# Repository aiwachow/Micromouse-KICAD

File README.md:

# Micromouse 2.0 class robot 
Micromouse is a autonomous robot whose purpose is to drive through the maze in the shortest time. 
This design include microcontrollers like STM32 and ESP32. Esp was added to testing over-the-air update  
and wireless communication for STM32. Walls are detecting by IR diodes and phototransistors. 

## Used software: 
 
## Things that have been tested and work:
- [x] Hardware 
- [x] STM32, flashing via ST-LINK  
- [x] Dc motors (with driver)
- [x] Encoders 
- [x] Proximity sensor 
- [ ] ESP32

## Software 

In the future, there will be a description of two approaches to the robot's software, as two two-person teams are working on the project.

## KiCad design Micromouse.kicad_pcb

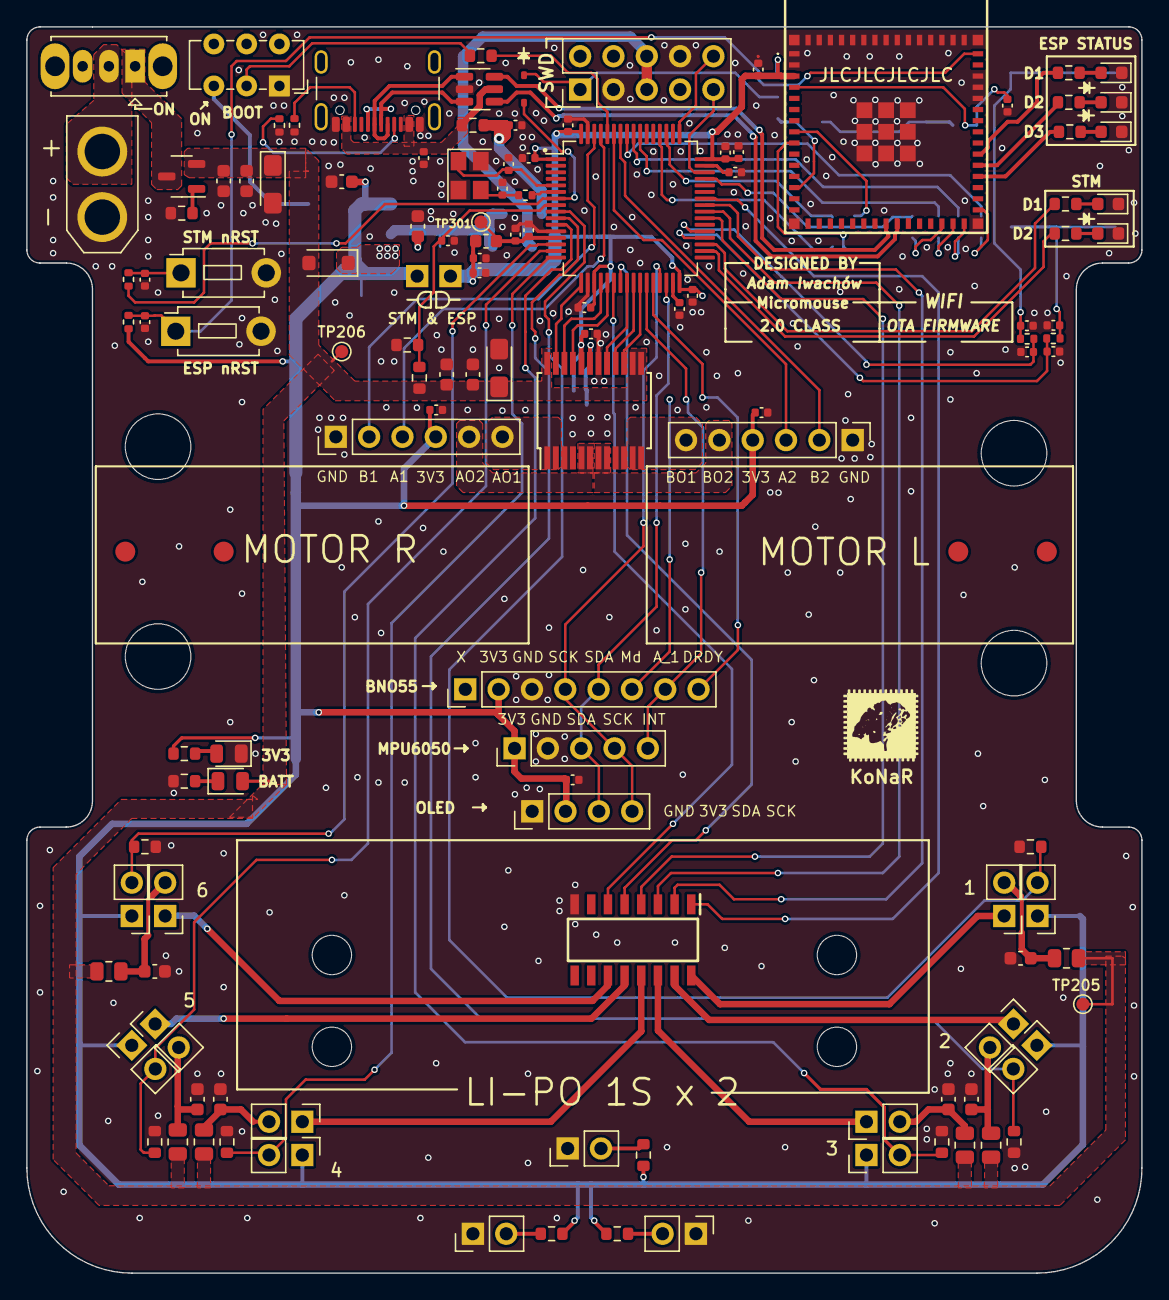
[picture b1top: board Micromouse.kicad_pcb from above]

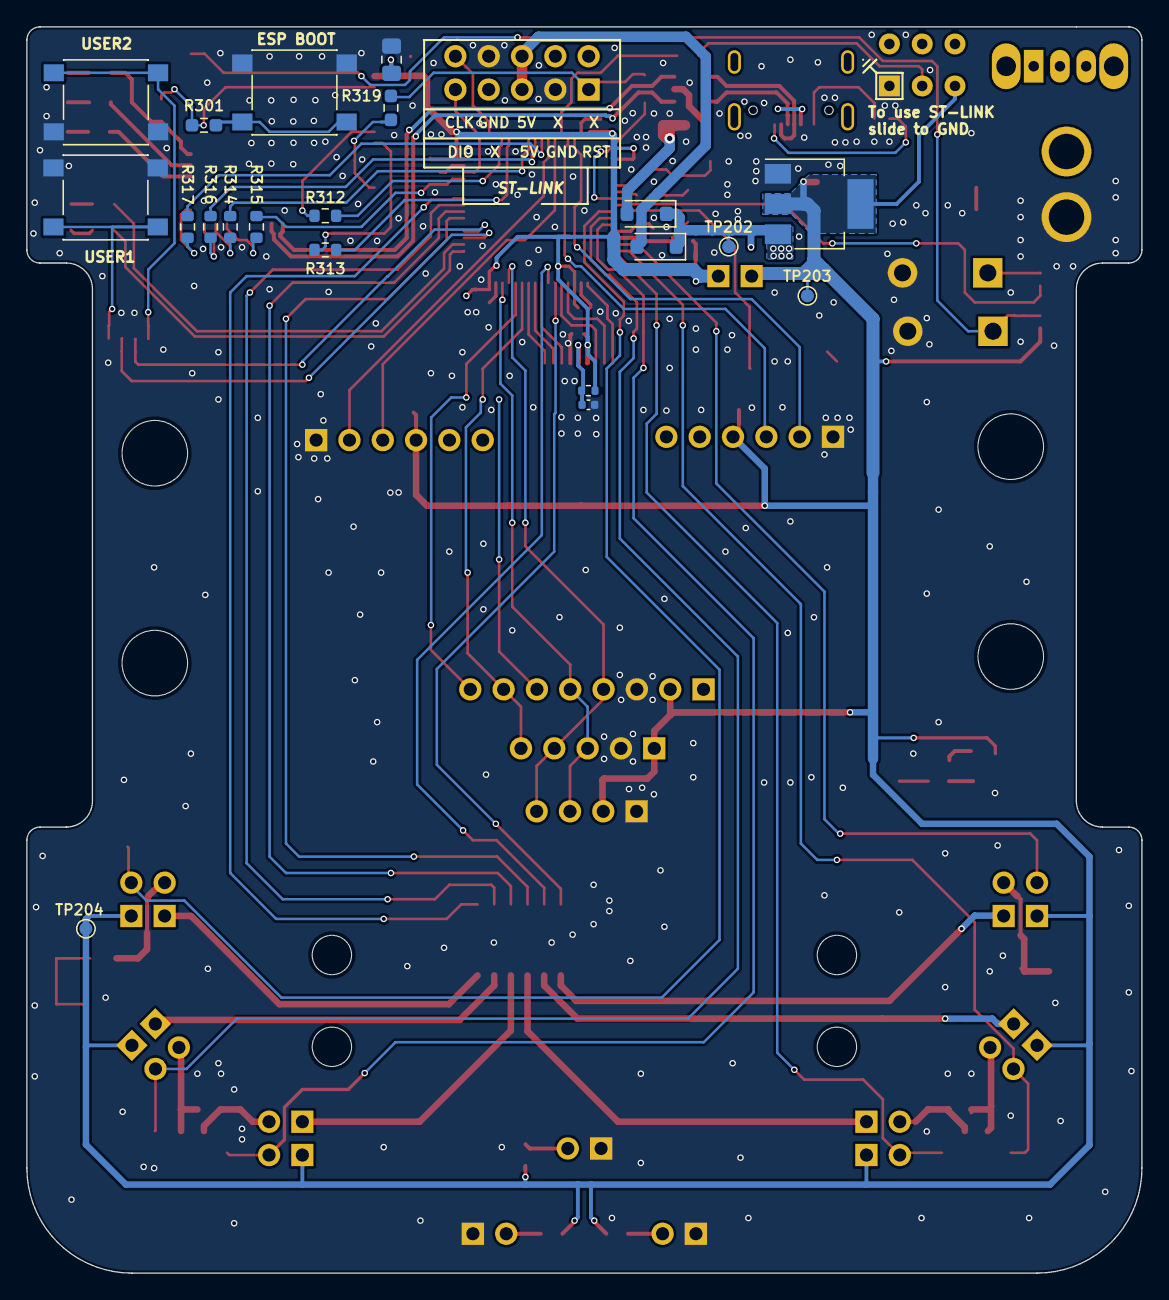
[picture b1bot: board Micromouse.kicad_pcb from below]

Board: 2 copper layers, 85.0 x 95.0 mm, 153 parts (20 on the bottom side), 108 nets.

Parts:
C201, C304, C306, C307, C309, C310, C312, C314, C315, C316, C317, C318, C319, C320, C321, C323, C324, C401, C404, C405, C406: 100n; C_0402_1005Metric
C202, C403, C407, C501, C502, C503, C504, C505, C506: 100n; C_0603_1608Metric
C203, C207: 1u; C_0603_1608Metric
C204, C308: 4u7; C_0402_1005Metric
C205, C402: 10u; CP_EIA-3216-10_Kemet-I_Pad1.58x1.35mm_HandSolder
C206: 10n; C_0402_1005Metric
C208: 4u7; C_0603_1608Metric
C301, C303: 1u; C_0402_1005Metric
C302, C305: 10p; C_0402_1005Metric
C311, C313: 2u2; C_0402_1005Metric
C322: 10u; C_0805_2012Metric_Pad1.18x1.45mm_HandSolder
D201, D202, D203: D_Schottky; D_SOD-123FL
D204: BATT_LED; LED_0805_2012Metric
D205: 3V3_LED; LED_0805_2012Metric
D302, D303, D305, D306, D307: LED_WHITE; D_0603_1608Metric
D304: D_Schottky; D_SOD-323
D501, D507, D509: SFH 4550; PinHeader_1x02_P2.54mm_Vertical
D502, D503, D504, D505, D506, D508: LED; PinHeader_1x02_P2.54mm_Vertical
FB301: Optionally; L_0603_1608Metric
H201, H202, H203, H204: MountingHole; MountingHole_3mm
H401, H402, H403, H404: MountingHole; MountingHole_5mm
IC302: ESP32-S3-MINI-1-N8; ESP32S3MINI1N8
IC501: ULN2003ADR; SOIC127P600X175-16N
J201: XT30; AMASS_XT30U-M_1x02_P5.0mm_Vertical
J202: USB_C_Receptacle_USB2.0; USB_C_Receptacle_GCT_USB4105-xx-A_16P_TopMnt_Horizontal
J301: Conn_02x05_Counter_Clockwise; PinHeader_2x05_P2.54mm_Vertical
J302: Conn_01x04; PinHeader_1x04_P2.54mm_Vertical
J401, J402: Conn_01x06; PinHeader_1x06_P2.54mm_Vertical
J601: Conn_01x08; PinHeader_1x08_P2.54mm_Vertical
J602: Conn_01x05; PinHeader_1x05_P2.54mm_Vertical
JP201: Jumper_2_Bridged; PinHeader_1x02_P2.54mm_Vertical
Q201: PMOS; SOT-23-3
Q501: SFH 300 FA-3/4; PinHeader_1x02_P2.54mm_Vertical
Q502, Q503, Q504, Q505, Q506: Q_Photo_NPN; PinHeader_1x02_P2.54mm_Vertical
R201, R202: 5k1; R_0402_1005Metric
R203, R306: 10k; R_0603_1608Metric
R204: 0; R_0603_1608Metric
R205: 82k; R_0603_1608Metric
R206: 51k; R_0603_1608Metric
R207: 2k2; R_0603_1608Metric
R208: 1K; R_0603_1608Metric
R301: 1k; R_0603_1608Metric_Pad0.98x0.95mm_HandSolder
R302, R305, R309, R310, R318, R501, R503, R505, R507, R509, R511, R513, R514, R515: 1k; R_0603_1608Metric
R303: 22; R_0402_1005Metric
R304, R311, R401: 10k; R_0402_1005Metric
R307, R308: 1k; R_0402_1005Metric
R312, R313: 100; R_0603_1608Metric
R314, R315, R316, R317: 22; R_0603_1608Metric
R319: 0; R_0603_1608Metric_Pad0.98x0.95mm_HandSolder
R502, R504, R506, R508, R510, R512: 47; R_0805_2012Metric
SW201: SW_SPDT; SW_Slide_1P2T_CK_OS102011MS2Q
SW301: NRST; SW_PUSH_1P1T_6x3.5mm_H4.3_APEM_MJTP1243
SW302: SW_SPDT; SW_E-Switch_EG1271_SPDT
SW303, SW304: USER; SW_Push_1P1T_NO_6x6mm_H9.5mm
SW305: ESP_RST; SW_PUSH_1P1T_6x3.5mm_H4.3_APEM_MJTP1243
SW306: BOOT; SW_Push_1P1T_NO_6x6mm_H9.5mm
TP202, TP203, TP204, TP205, TP206, TP301: TestPoint; TestPoint_Pad_D1.0mm
U201: USBLC6-2SC6; SOT-23-6
U202: LDL1117S33R; SOT-223-3_TabPin2
U301: STM32F405RGT6; LQFP-64_10x10mm_P0.5mm
U401: TB6612FNG; SSOP-24_5.3x8.2mm_P0.65mm
Y301: 16MHz|9p|10ppm; Crystal_SMD_3225-4Pin_3.2x2.5mm

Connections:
5V_ST: D203.2 (A), J301.5, J301.6
+3.3V: C208.1, C301.1, C306.1, C308.1, C309.1, C310.1, C312.1, C314.1, C315.1, C321.1, C322.1, C323.1, C404.1, C405.1, C406.1, FB301.1, IC302.3 (3V3), J302.2 (Pin_1), J401.4 (Pin_1), J402.4 (Pin_1), J601.2, J602.1, JP201.1 (A), JP201.2 (B), Q501.1 (C), Q502.1 (C), Q503.1 (C), Q504.1 (C), Q505.1 (C), Q506.1 (C), R208.1, R311.2, R401.1, R513.2, R514.2, R515.2, SW302.3 (C), TP203.1, TP204.1, U202.2 (VO), U301.1 (VBAT), U301.19 (VDD), U301.32 (VDD), U301.48 (VDD), U301.64 (VDD), U401.20 (VCC)
+3.3VA: C303.1, C307.1, FB301.2, TP301.1, U301.13 (VDDA)
+BATT: C202.1, C203.1, C205.1, C402.1, C403.1, C407.1, D202.2 (A), D204.2 (A), Q201.2 (S), R205.2, R502.1, R504.1, R506.1, R508.1, R510.1, R512.1, TP205.1, TP206.1, U401.13 (VM2), U401.14 (VM3), U401.24 (VM1)
/Distance_sensors/Emitter1A: C504.1, D504.2 (A), R508.2
/Distance_sensors/Emitter2A: C503.1, D503.2 (A), R506.2
/Distance_sensors/Emitter3A: C502.1, D502.2 (A), R504.2
/Distance_sensors/Emitter4A: C501.1, D501.2 (A), R502.2
/Distance_sensors/Emitter5A: C505.1, D505.2 (A), R510.2
/Distance_sensors/Emitter6A: C506.1, D506.2 (A), R512.2
/Distance_sensors/Emitter_1: D504.1 (K), IC501.13 (4C)
/Distance_sensors/Emitter_2: D503.1 (K), IC501.14 (3C)
/Distance_sensors/Emitter_3: D502.1 (K), IC501.15 (2C)
/Distance_sensors/Emitter_4: D501.1 (K), IC501.16 (1C)
/Distance_sensors/Emitter_5: D505.1 (K), IC501.12 (5C)
/Distance_sensors/Emitter_6: D506.1 (K), IC501.11 (6C)
/Microcontroller/HSE OUT: C305.1, R303.2, Y301.3
/Microcontroller/OTA_RX: IC302.9 (IO5), R313.2
/Microcontroller/OTA_TX: IC302.8 (IO4), R312.2
/Microcontroller/USER_LD2_A: D302.2 (A), R302.2
/Microcontroller/USER_LD2_A_esp: D306.2 (A), R310.2
/Microcontroller/USER_LD3_A: D303.2 (A), R305.2
/Microcontroller/USER_LD3_A_esp: D307.2 (A), R318.2
/Microcontroller/USER_LD_A_esp: D305.2 (A), R309.2
/Motors/AO1: J401.6 (Pin_3), U401.1 (AO1), U401.2 (AO1)
/Motors/AO2: J401.5, U401.5 (AO2), U401.6 (AO2)
/Motors/BO1: J402.6 (Pin_3), U401.11 (BO1), U401.12 (BO1)
/Motors/BO2: J402.5, U401.7 (BO2), U401.8 (BO2)
/Power/8V_BATT: J201.2, SW201.2 (B)
/Power/DN: J202.A7 (D-), J202.B7 (D-), U201.1 (I/O1)
/Power/DP: J202.A6 (D+), J202.B6 (D+), U201.3 (I/O2)
/Power/D_PMOS: Q201.3 (D), SW201.1 (A)
/Power/LDO_VIN: C207.1, D201.1 (K), D202.1 (K), D203.1 (K), TP202.1, U202.3 (VI)
/Power/usb_vin: C204.1, D201.2 (A), R204.2
BOOT: C324.1, IC302.4 (IO0), R301.2
BatteryLEVEL: C206.1, R205.1, R206.2, U301.8 (PC0)
DRDY: J601.8 (Pin_3), U301.28 (PB2)
ESP_USB_DN: IC302.23 (IO19), U201.6 (I/O1)
ESP_USB_DP: IC302.24 (IO20), U201.4 (I/O2)
GND: C201.2, C202.2, C203.2, C204.2, C205.2, C206.2, C207.2, C208.2, C301.2, C302.2, C303.2, C304.2, C305.2, C306.2, C307.2, C308.2, C309.2, C310.2, C311.2, C312.2, C313.2, C314.2, C315.2, C316.2, C317.2, C318.1, C319.1, C320.2, C321.2, C322.2, C323.2, C324.2, C401.2, C402.2, C403.2, C404.2, C405.2, C406.2, C407.2, C501.2, C502.2, C503.2, C504.2, C505.2, C506.2, D205.1 (K), D302.1 (K), D303.1 (K), D305.1 (K), D306.1 (K), D307.1 (K), D507.1 (K), D508.1 (K), D509.1 (K), IC302.1 (GND_1), IC302.2 (GND_2), IC302.41 (IO45), IC302.42 (GND_3), IC302.43 (GND_4), IC302.46 (GND_5), IC302.47 (GND_6), IC302.48 (GND_7), IC302.49 (GND_8), IC302.50 (GND_9), IC302.51 (GND_10), IC302.52 (GND_11), IC302.53 (GND_12), IC302.54 (GND_13), IC302.55 (GND_14), IC302.56 (GND_15), IC302.57 (GND_16), IC302.58 (GND_17), IC302.59 (GND_18), IC302.60 (GND_19), IC302.61 (GND_20), IC302.62 (GND_21), IC302.63 (GND_22), IC302.64 (GND_23), IC302.65 (GND_24), IC302.66 (GND_25), IC302.67 (GND_26), IC302.68 (GND_27), IC302.69 (GND_28), IC302.70 (GND_29), IC302.71 (GND_30), IC302.72 (GND_31), IC302.73 (GND_32), IC501.8 (E), J201.1, J202.A1 (GND), J202.A12 (GND), J202.B1 (GND), J202.B12 (GND), J301.3, J301.8, J302.1 (Pin_4), J401.1 (Pin_6), J402.1 (Pin_6), J601.3 (Pin_8), J602.2 (Pin_5), R201.2, R202.2, R203.1, R206.1, R207.1, R501.1, R503.1, R505.1, R507.1, R509.1, R511.1, SW301.2 (B), SW302.1 (A), SW303.2 (B), SW304.2 (B), SW305.2 (B), SW306.2 (B), U201.2 (GND), U202.1 (GND), U301.12 (VSSA), U301.18 (VSS), U301.63 (VSS), U401.3 (PGND1), U401.4 (PGND1), U401.9 (PGND2), U401.10 (PGND2), U401.18 (GND), Y301.2, Y301.4
HSE_IN: C302.1, U301.5 (PH0), Y301.1
HSE_OUT: R303.1, U301.6 (PH1)
I2C1_SCK: J302.4 (Pin_3), J601.4, J602.4, U301.29 (PB10)
I2C1_SDA: J302.3 (Pin_2), J601.5, J602.3, U301.30 (PB11)
IMU_INT: J601.7, J602.5 (Pin_2), U301.27 (PB1)
IR_1: IC501.4 (4B), U301.39 (PC8)
IR_2: IC501.3 (3B), U301.40 (PC9)
IR_3: IC501.2 (2B), U301.41 (PA8)
IR_4: IC501.1 (1B), U301.42 (PA9)
IR_5: IC501.5 (5B), U301.23 (PA7)
IR_6: IC501.6 (6B), U301.22 (PA6)
MotorL_BIN1: U301.24 (PC4), U401.17 (BIN1)
MotorL_BIN2: U301.25 (PC5), U401.16 (BIN2)
MotorL_PWM: U301.26 (PB0), U401.15 (PWMB)
MotorR_AIN1: U301.21 (PA5), U401.21 (AIN1)
MotorR_AIN2: U301.20 (PA4), U401.22 (AIN2)
MotorR_PWM: U301.17 (PA3), U401.23 (PWMA)
NRST: D304.2 (A), R304.2, U301.7 (NRST)
unnamed: C304.1, R304.1, SW301.1 (A)
unnamed: C316.1, R307.1, SW303.1 (A)
unnamed: C319.2, R308.2, SW304.1 (A)
unnamed: D204.1 (K), R207.2
unnamed: D205.2 (A), R208.2
unnamed: D507.2 (A), R513.1
unnamed: D508.2 (A), R514.1
unnamed: D509.2 (A), R515.1
unnamed: C320.1, IC302.45 (EN), R311.1, SW305.1 (A)
unnamed: IC302.13 (IO9), R319.2
unnamed: IC302.28 (IO33), R315.2
unnamed: IC302.29 (IO34), R314.2
unnamed: IC302.31 (IO35), R317.2
unnamed: IC302.30 (IO48), R316.2
unnamed: J202.A5 (CC1), R201.1
unnamed: J202.B5 (CC2), R202.1
unnamed: Q201.1 (G), R203.2
unnamed: R301.1, SW306.1 (A)
unnamed: R306.1, SW302.2 (B)
unnamed: R306.2, U301.60 (BOOT0)
unnamed: C311.1, U301.31 (VCAP_1)
unnamed: C313.1, U301.47 (VCAP_2)
unnamed: C401.1, R401.2, U401.19 (STBY)
REC_1: Q504.2 (E), R507.2, U301.9 (PC1)
REC_2: Q503.2 (E), R505.2, U301.10 (PC2)
REC_3: Q502.2 (E), R503.2, U301.11 (PC3)
REC_4: Q501.2 (E), R501.2, U301.16 (PA2)
REC_5: Q505.2 (E), R509.2, U301.15 (PA1)
REC_6: Q506.2 (E), R511.2, U301.14 (PA0)
SPI1_CS_ESP: R315.1, U301.45 (PA12)
SPI1_MISO_ESP: R316.1, U301.56 (PB4)
SPI1_MOSI_ESP: R317.1, U301.57 (PB5)
SPI1_SCK_ESP: R314.1, U301.55 (PB3)
SWCLK: J301.10, U301.49 (PA14)
SWDIO: J301.9, U301.46 (PA13)
TIM_ENCODER_A1: J401.3 (Pin_4), U301.61 (PB8)
TIM_ENCODER_A2: J402.3 (Pin_4), U301.59 (PB7)
TIM_ENCODER_B1: J401.2, U301.62 (PB9)
TIM_ENCODER_B2: J402.2, U301.58 (PB6)
UART4_RX_OTA: R313.1, U301.52 (PC11)
UART4_TX_OTA: R312.1, U301.51 (PC10)
USER_B: C317.1, R307.2, U301.36 (PB15)
USER_B2: C318.2, R308.1, U301.37 (PC6)
USER_LD2: R302.1, U301.34 (PB13)
USER_LD2_esp: IC302.35 (IO39), R310.1
USER_LD3: R305.1, U301.35 (PB14)
USER_LD3_esp: IC302.36 (IO40), R318.1
USER_LD_esp: IC302.34 (IO38), R309.1
VBUS: C201.1, J202.A4 (VBUS), J202.A9 (VBUS), J202.B4 (VBUS), J202.B9 (VBUS), R204.1, U201.5 (VBUS)
_NRST: D304.1 (K), J301.1, R319.1

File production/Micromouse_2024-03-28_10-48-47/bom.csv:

Designator,Footprint,Quantity,Value,LCSC Part #
"C201, C304, C306, C307, C309, C310, C312, C314, C315, C316, C317, C318, C319, C320, C321, C323, C324, C401, C404, C405, C406",0402,21,100n,C307331
"C202, C403, C407, C501, C502, C503, C504, C505, C506",0603,9,100n,C14663
"C203, C207",0603,2,1u,C15849
C204,0402,1,4u7,C23733
"C205, C402",CP_EIA-3216-10_Kemet-I_Pad1.58x1.35mm_HandSolder,2,10u,C7171
C206,0402,1,10n,C15195
C208,0603,1,4u7,C19666 
"C301, C303",0402,2,1u,C15849
"C302, C305",0402,2,10p,C32949
C308,0402,1,4u7,C96446
"C311, C313",0402,2,2u2,C12530
C322,0805,1,10u,C307331
"D201, D202, D203",D_SOD-123FL,3,D_Schottky,
D204,0805,1,BATT_LED,C2297
D205,0805,1,3V3_LED,C2297
"D302, D303, D305, D306, D307",0603,5,LED_WHITE,C2290
D304,D_SOD-323,1,D_Schottky,C191023
"D501, D507, D509",PinHeader_1x02_P2.54mm_Vertical,3,SFH 4550,
"D502, D503, D504, D505, D506, D508",PinHeader_1x02_P2.54mm_Vertical,6,LED,
FB301,0603,1,Optionally,C1002
"H201, H202, H203, H204",MountingHole_3mm,4,MountingHole,
"H401, H402, H403, H404",MountingHole_5mm,4,MountingHole,
IC302,ESP32S3MINI1N8,1,ESP32-S3-MINI-1-N8,
IC501,SOIC127P600X175-16N,1,ULN2003ADR,
J201,AMASS_XT30U-M_1x02_P5.0mm_Vertical,1,XT30,
J202,USB_C_Receptacle_GCT_USB4105-xx-A_16P_TopMnt_Horizontal,1,USB_C_Receptacle_USB2.0,
J301,PinHeader_2x05_P2.54mm_Vertical,1,Conn_02x05_Counter_Clockwise,
J302,PinHeader_1x04_P2.54mm_Vertical,1,Conn_01x04,
"J401, J402",PinHeader_1x06_P2.54mm_Vertical,2,Conn_01x06,
J601,PinHeader_1x08_P2.54mm_Vertical,1,Conn_01x08,
J602,PinHeader_1x05_P2.54mm_Vertical,1,Conn_01x05,
JP201,PinHeader_1x02_P2.54mm_Vertical,1,Jumper_2_Bridged,
Q201,SOT-23-3,1,PMOS,C15127
Q501,PinHeader_1x02_P2.54mm_Vertical,1,SFH 300 FA-3/4,
"Q502, Q503, Q504, Q505, Q506",PinHeader_1x02_P2.54mm_Vertical,5,Q_Photo_NPN,
"R201, R202",0402,2,5k1,C25905
R203,0603,1,10k,C25804
R204,0603,1,0,C21189
R205,0603,1,82k,C23254
R206,0603,1,51k,C23196
R207,0603,1,2k2,C4190
"R208, R302, R305, R309, R310, R318, R501, R503, R505, R507, R509, R511, R513, R514, R515",0603,15,1K,C21190
R301,0603,1,1k,
R303,0402,1,22,C25092
"R304, R311, R401",0402,3,10k,C25744
R306,0603,1,10k,C25744
"R307, R308",0402,2,1k,C11702
"R312, R313",0603,2,100,
"R314, R315, R316",0603,3,22,
R317,0603,1,22,
R319,0603,1,0,
"R502, R504, R506, R508, R510, R512",0805,6,47,C17714
SW201,SW_Slide_1P2T_CK_OS102011MS2Q,1,SW_SPDT,
SW301,SW_PUSH_1P1T_6x3.5mm_H4.3_APEM_MJTP1243,1,NRST,
SW302,SW_E-Switch_EG1271_SPDT,1,SW_SPDT,
"SW303, SW304",SW_Push_1P1T_NO_6x6mm_H9.5mm,2,USER,
SW305,SW_PUSH_1P1T_6x3.5mm_H4.3_APEM_MJTP1243,1,ESP_RST,
SW306,SW_Push_1P1T_NO_6x6mm_H9.5mm,1,BOOT,
"TP202, TP203, TP204, TP205, TP206, TP301",TestPoint_Pad_D1.0mm,6,TestPoint,
U201,SOT-23-6,1,USBLC6-2SC6,
U202,SOT-223-3_TabPin2,1,LDL1117S33R,
U301,LQFP-64_10x10mm_P0.5mm,1,STM32F405RGT6,C15742
U401,SSOP-24_5.3x8.2mm_P0.65mm,1,TB6612FNG,
Y301,Crystal_SMD_3225-4Pin_3.2x2.5mm,1,16MHz|9p|10ppm,C13738

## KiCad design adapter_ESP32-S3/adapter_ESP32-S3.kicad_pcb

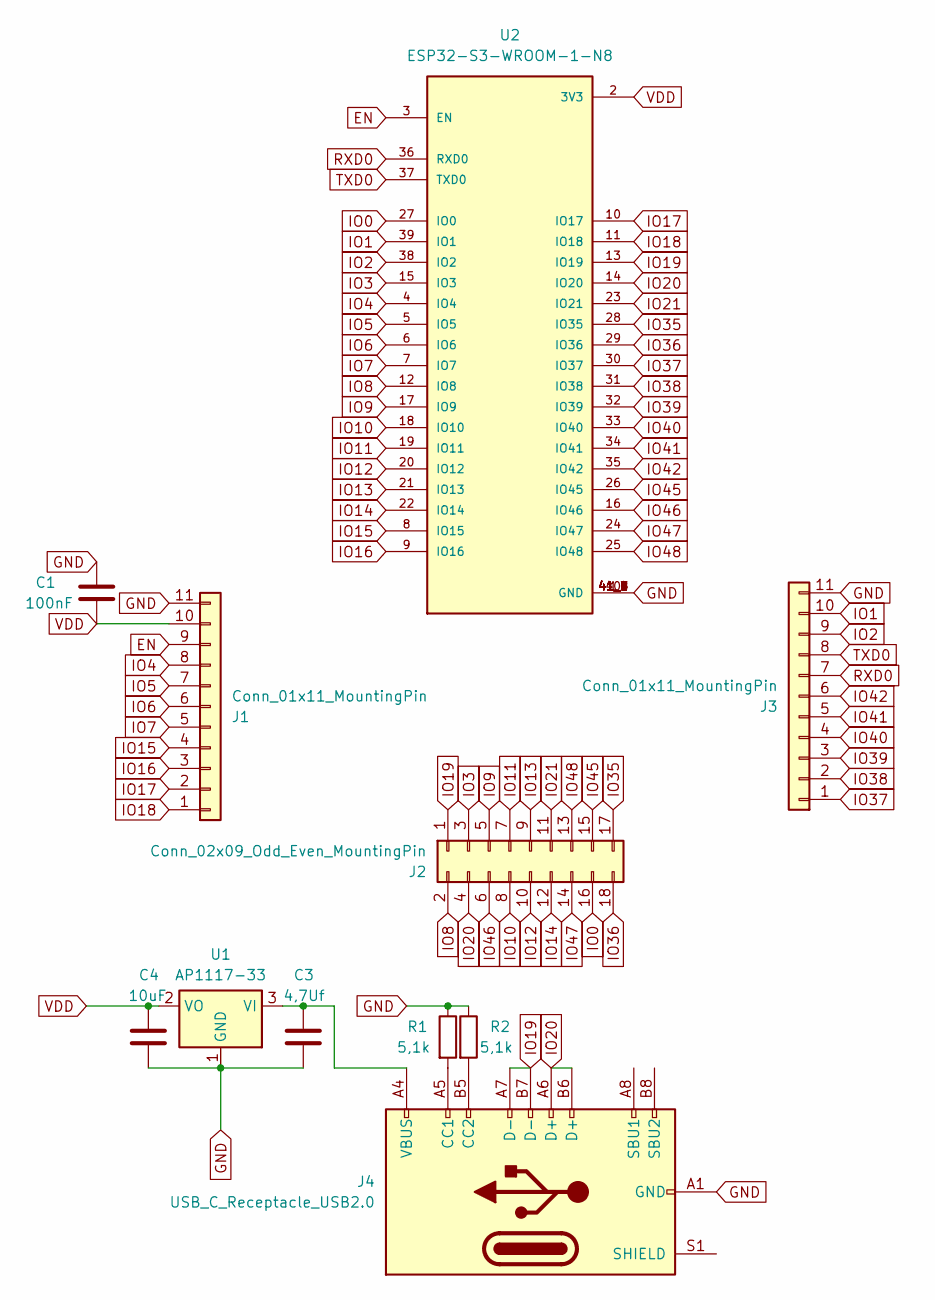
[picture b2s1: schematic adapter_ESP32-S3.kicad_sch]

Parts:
C1: 100nF; C_0603_1608Metric
C3: 4,7Uf; C_0603_1608Metric
C4: 10uF; C_0603_1608Metric
J1, J3: Conn_01x11_MountingPin; PinHeader_1x11_P2.54mm_Vertical
J2: Conn_02x09_Odd_Even_MountingPin; PinHeader_2x09_P2.54mm_Vertical
J4: USB_C_Receptacle_USB2.0; USB_C_Receptacle_GCT_USB4105-xx-A_16P_TopMnt_Horizontal
R1, R2: 5,1k; R_0603_1608Metric
U1: AP1117-33; SOT-223-3_TabPin2
U2: ESP32-S3-WROOM-1-N8; XCVR_ESP32-S3-WROOM-1-N8

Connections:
EN: J1.9, U2.3 (EN)
GND: C1.2, C3.1, C4.1, J1.11, J3.11, J4.A1 (GND), J4.A12 (GND), J4.B1 (GND), J4.B12 (GND), R1.1, R2.1, U1.1 (GND), U2.1 (GND), U2.40 (GND), U2.41_1 (GND), U2.41_2 (GND), U2.41_3 (GND), U2.41_4 (GND), U2.41_5 (GND), U2.41_6 (GND), U2.41_7 (GND), U2.41_8 (GND), U2.41_9 (GND)
IO0: J2.16, U2.27 (IO0)
IO1: J3.10, U2.39 (IO1)
IO2: J3.9, U2.38 (IO2)
IO3: J2.3, U2.15 (IO3)
IO4: J1.8, U2.4 (IO4)
IO5: J1.7, U2.5 (IO5)
IO6: J1.6, U2.6 (IO6)
IO7: J1.5, U2.7 (IO7)
IO8: J2.2, U2.12 (IO8)
IO9: J2.5, U2.17 (IO9)
IO10: J2.8, U2.18 (IO10)
IO11: J2.7, U2.19 (IO11)
IO12: J2.10, U2.20 (IO12)
IO13: J2.9, U2.21 (IO13)
IO14: J2.12, U2.22 (IO14)
IO15: J1.4, U2.8 (IO15)
IO16: J1.3, U2.9 (IO16)
IO17: J1.2, U2.10 (IO17)
IO18: J1.1, U2.11 (IO18)
IO19: J2.1, J4.A7 (D-), J4.B7 (D-), U2.13 (IO19)
IO20: J2.4, J4.A6 (D+), J4.B6 (D+), U2.14 (IO20)
IO21: J2.11, U2.23 (IO21)
IO35: J2.17, U2.28 (IO35)
IO36: J2.18, U2.29 (IO36)
IO37: J3.1, U2.30 (IO37)
IO38: J3.2, U2.31 (IO38)
IO39: J3.3, U2.32 (IO39)
IO40: J3.4, U2.33 (IO40)
IO41: J3.5, U2.34 (IO41)
IO42: J3.6, U2.35 (IO42)
IO45: J2.15, U2.26 (IO45)
IO46: J2.6, U2.16 (IO46)
IO47: J2.14, U2.24 (IO47)
IO48: J2.13, U2.25 (IO48)
unnamed: J4.A5 (CC1), R1.2
unnamed: J4.B5 (CC2), R2.2
unnamed: C3.2, J4.A4 (VBUS), J4.A9 (VBUS), J4.B4 (VBUS), J4.B9 (VBUS), U1.3 (VI)
RXD0: J3.7, U2.36 (RXD0)
TXD0: J3.8, U2.37 (TXD0)
VDD: C1.1, C4.2, J1.10, U1.2 (VO), U2.2 (3V3)

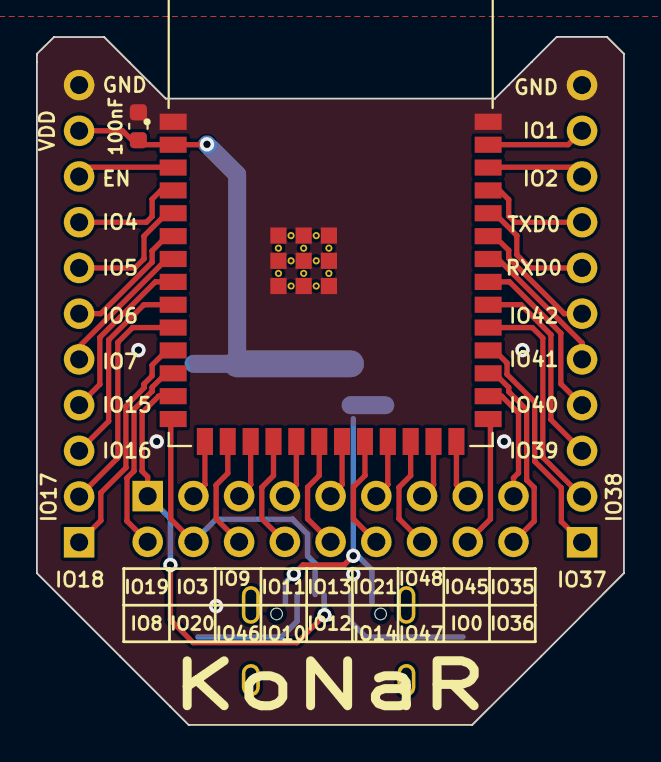
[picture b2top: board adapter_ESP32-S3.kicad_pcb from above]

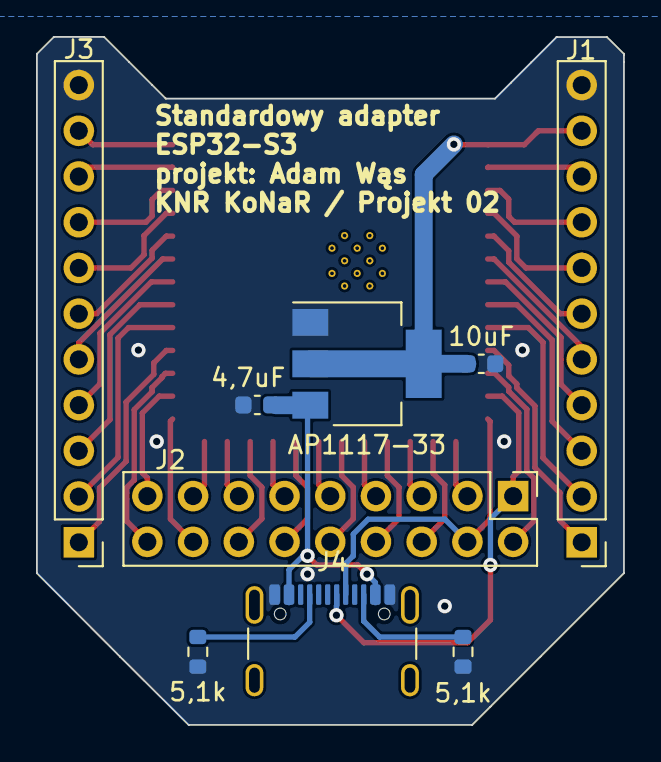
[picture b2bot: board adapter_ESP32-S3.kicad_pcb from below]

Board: 2 copper layers, 32.6 x 38.2 mm, 11 parts (9 on the bottom side), 42 nets.

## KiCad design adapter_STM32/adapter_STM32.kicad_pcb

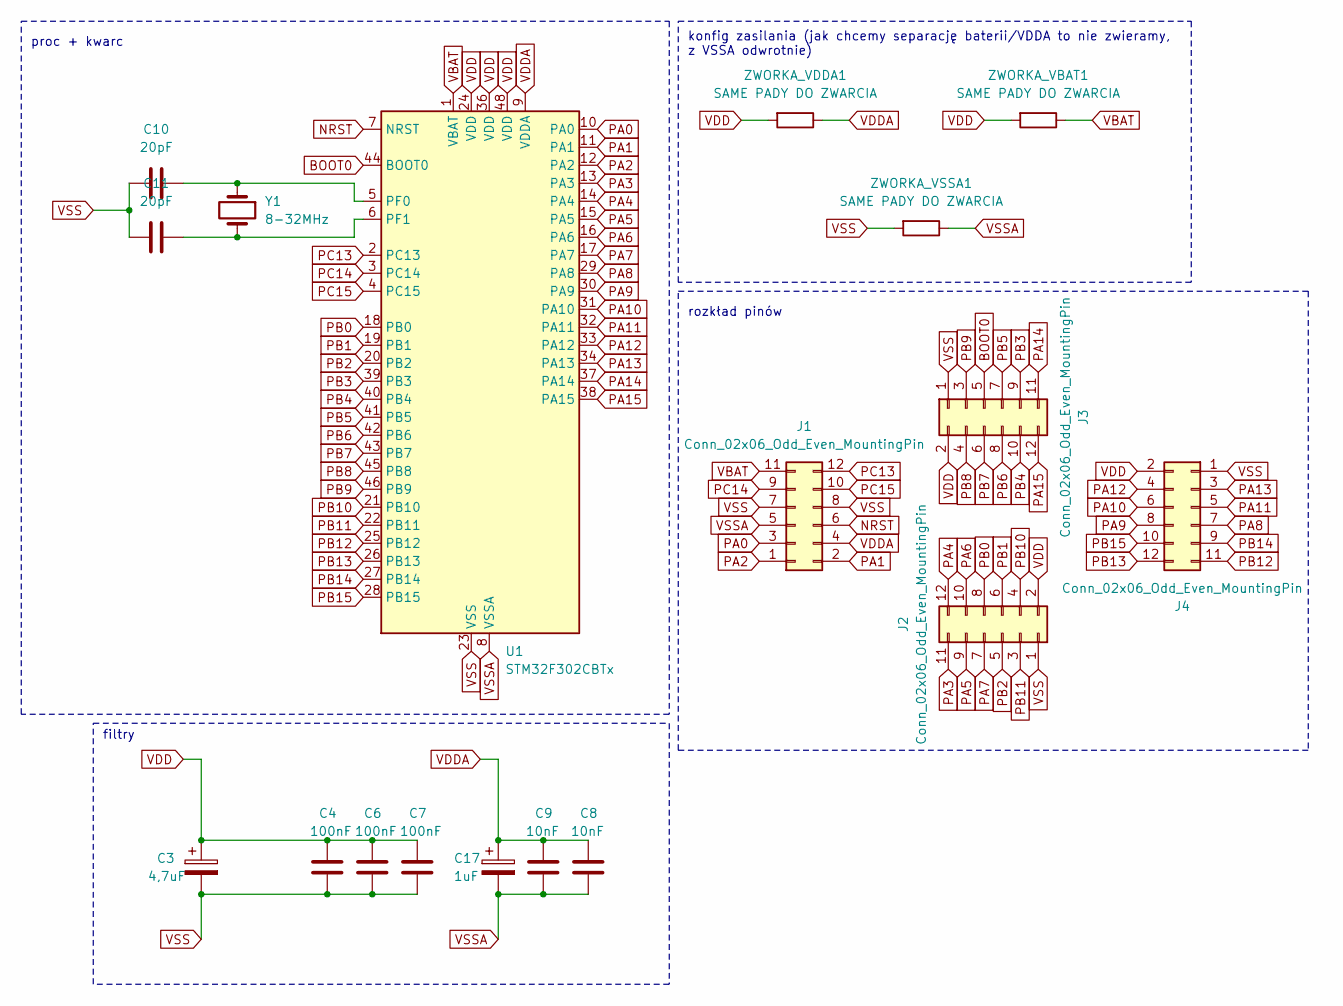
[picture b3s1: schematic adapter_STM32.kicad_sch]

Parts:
C3: 4,7uF; CP_Radial_D5.0mm_P2.00mm
C4, C6, C7: 100nF; C_0402_1005Metric
C8, C9: 10nF; C_0402_1005Metric
C10, C11: 20pF; C_0603_1608Metric
C17: 1uF; CP_Radial_D5.0mm_P2.00mm
J1, J2, J3, J4: Conn_02x06_Odd_Even_MountingPin; PinHeader_2x06_P2.54mm_Vertical
U1: STM32F302CBTx; LQFP-48_7x7mm_P0.5mm
Y1: 8-32MHz; Crystal_SMD_5032-2Pin_5.0x3.2mm
ZWORKA_VBAT1: SAME PADY DO ZWARCIA; R_0201_0603Metric
ZWORKA_VDDA1: SAME PADY DO ZWARCIA; R_0201_0603Metric
ZWORKA_VSSA1: SAME PADY DO ZWARCIA; R_0201_0603Metric

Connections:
BOOT0: J3.5, U1.44 (BOOT0)
NRST: J1.6, U1.7 (NRST)
unnamed: C10.1, U1.5 (PF0), Y1.1
unnamed: C11.1, U1.6 (PF1), Y1.2
PA0: J1.3, U1.10 (PA0)
PA1: J1.2, U1.11 (PA1)
PA2: J1.1, U1.12 (PA2)
PA3: J2.11, U1.13 (PA3)
PA4: J2.12, U1.14 (PA4)
PA5: J2.9, U1.15 (PA5)
PA6: J2.10, U1.16 (PA6)
PA7: J2.7, U1.17 (PA7)
PA8: J4.7, U1.29 (PA8)
PA9: J4.8, U1.30 (PA9)
PA10: J4.6, U1.31 (PA10)
PA11: J4.5, U1.32 (PA11)
PA12: J4.4, U1.33 (PA12)
PA13: J4.3, U1.34 (PA13)
PA14: J3.11, U1.37 (PA14)
PA15: J3.12, U1.38 (PA15)
PB0: J2.8, U1.18 (PB0)
PB1: J2.6, U1.19 (PB1)
PB2: J2.5, U1.20 (PB2)
PB3: J3.9, U1.39 (PB3)
PB4: J3.10, U1.40 (PB4)
PB5: J3.7, U1.41 (PB5)
PB6: J3.8, U1.42 (PB6)
PB7: J3.6, U1.43 (PB7)
PB8: J3.4, U1.45 (PB8)
PB9: J3.3, U1.46 (PB9)
PB10: J2.4, U1.21 (PB10)
PB11: J2.3, U1.22 (PB11)
PB12: J4.11, U1.25 (PB12)
PB13: J4.12, U1.26 (PB13)
PB14: J4.9, U1.27 (PB14)
PB15: J4.10, U1.28 (PB15)
PC13: J1.12, U1.2 (PC13)
PC14: J1.9, U1.3 (PC14)
PC15: J1.10, U1.4 (PC15)
VBAT: J1.11, U1.1 (VBAT), ZWORKA_VBAT1.1
VDD: C3.1, C4.1, C6.1, C7.1, J2.2, J3.2, J4.2, U1.24 (VDD), U1.36 (VDD), U1.48 (VDD), ZWORKA_VBAT1.2, ZWORKA_VDDA1.2
VDDA: C8.1, C9.1, C17.1, J1.4, U1.9 (VDDA), ZWORKA_VDDA1.1
VSS: C3.2, C4.2, C6.2, C7.2, C10.2, C11.2, J1.7, J1.8, J2.1, J3.1, J4.1, U1.23 (VSS), U1.35 (VSS), U1.47 (VSS), ZWORKA_VSSA1.2
VSSA: C8.2, C9.2, C17.2, J1.5, U1.8 (VSSA), ZWORKA_VSSA1.1

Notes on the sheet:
filtry
proc + kwarc
rozkład pinów
konfig zasilania (jak chcemy separację baterii/VDDA to nie zwieramy, z VSSA odwrotnie)

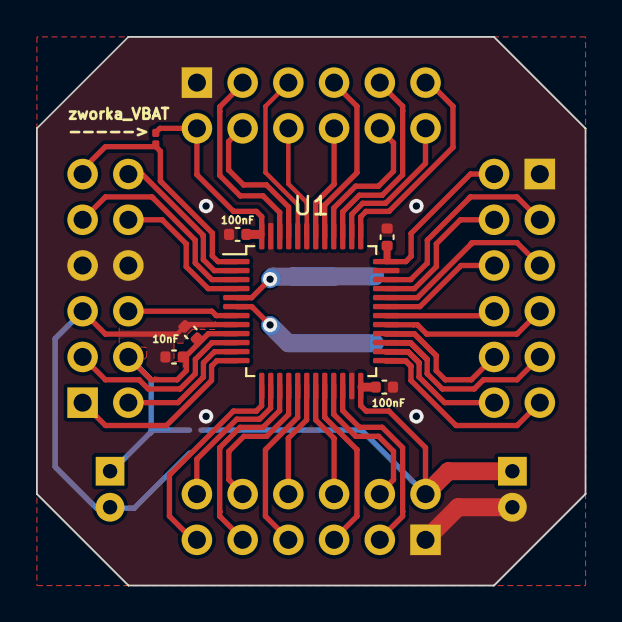
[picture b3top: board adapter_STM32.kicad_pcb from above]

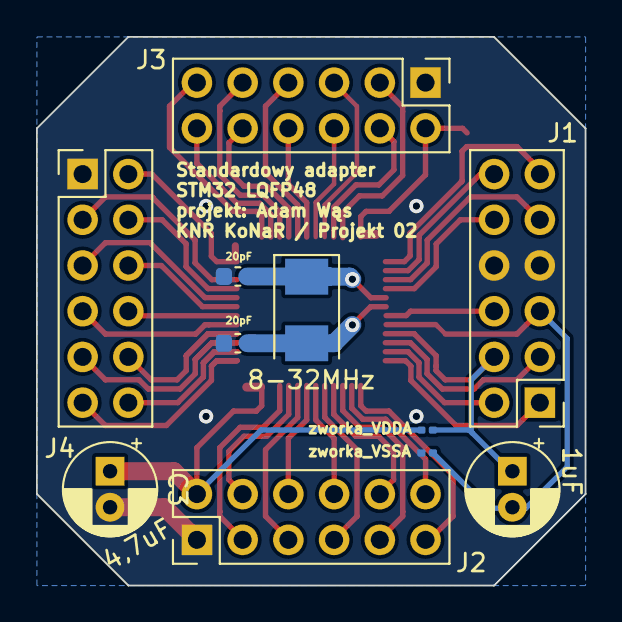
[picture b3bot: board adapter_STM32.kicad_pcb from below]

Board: 2 copper layers, 30.5 x 30.5 mm, 18 parts (11 on the bottom side), 44 nets.

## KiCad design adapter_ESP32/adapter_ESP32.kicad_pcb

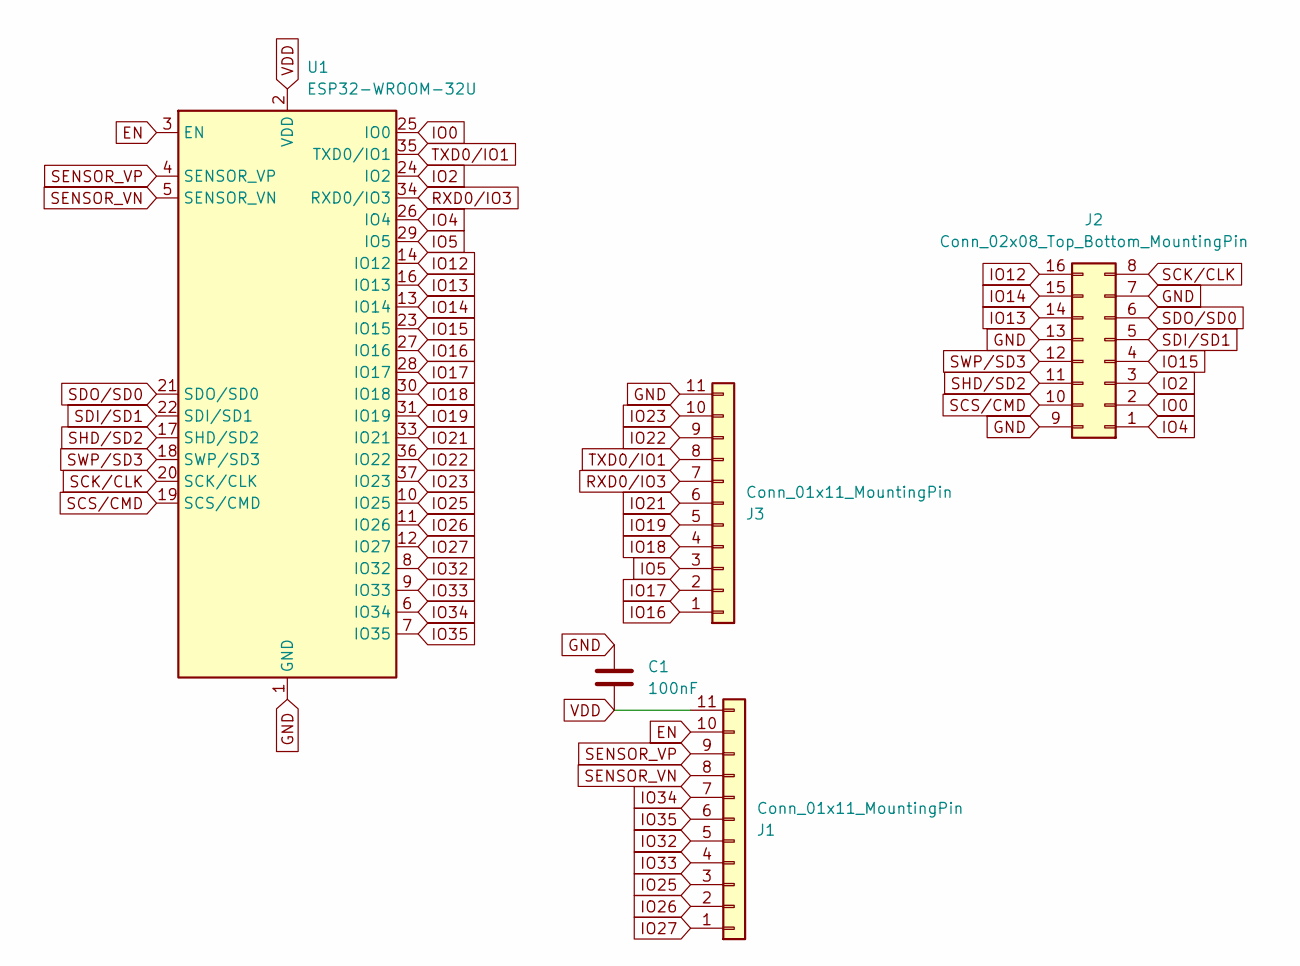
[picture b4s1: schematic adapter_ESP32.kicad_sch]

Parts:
C1: 100nF; C_0603_1608Metric
J1, J3: Conn_01x11_MountingPin; PinHeader_1x11_P2.54mm_Vertical
J2: Conn_02x08_Top_Bottom_MountingPin; PinHeader_2x08_P2.54mm_Vertical
U1: ESP32-WROOM-32U

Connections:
EN: J1.10, U1.3 (EN)
GND: C1.2, J2.7, J2.9, J2.13, J3.11, U1.1 (GND), U1.15 (GND), U1.38 (GND), U1.39 (GND)
IO0: J2.2, U1.25 (IO0)
IO2: J2.3, U1.24 (IO2)
IO4: J2.1, U1.26 (IO4)
IO5: J3.3, U1.29 (IO5)
IO12: J2.16, U1.14 (IO12)
IO13: J2.14, U1.16 (IO13)
IO14: J2.15, U1.13 (IO14)
IO15: J2.4, U1.23 (IO15)
IO16: J3.1, U1.27 (IO16)
IO17: J3.2, U1.28 (IO17)
IO18: J3.4, U1.30 (IO18)
IO19: J3.5, U1.31 (IO19)
IO21: J3.6, U1.33 (IO21)
IO22: J3.9, U1.36 (IO22)
IO23: J3.10, U1.37 (IO23)
IO25: J1.3, U1.10 (IO25)
IO26: J1.2, U1.11 (IO26)
IO27: J1.1, U1.12 (IO27)
IO32: J1.5, U1.8 (IO32)
IO33: J1.4, U1.9 (IO33)
IO34: J1.7, U1.6 (IO34)
IO35: J1.6, U1.7 (IO35)
RXD0/IO3: J3.7, U1.34 (RXD0/IO3)
SCK/CLK: J2.8, U1.20 (SCK/CLK)
SCS/CMD: J2.10, U1.19 (SCS/CMD)
SDI/SD1: J2.5, U1.22 (SDI/SD1)
SDO/SD0: J2.6, U1.21 (SDO/SD0)
SENSOR_VN: J1.8, U1.5 (SENSOR_VN)
SENSOR_VP: J1.9, U1.4 (SENSOR_VP)
SHD/SD2: J2.11, U1.17 (SHD/SD2)
SWP/SD3: J2.12, U1.18 (SWP/SD3)
TXD0/IO1: J3.8, U1.35 (TXD0/IO1)
VDD: C1.1, J1.11, U1.2 (VDD)

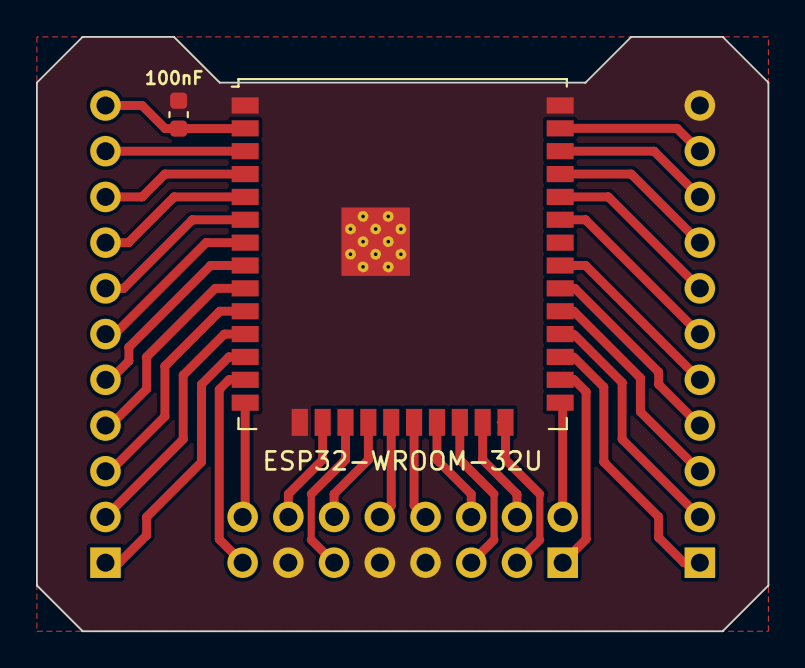
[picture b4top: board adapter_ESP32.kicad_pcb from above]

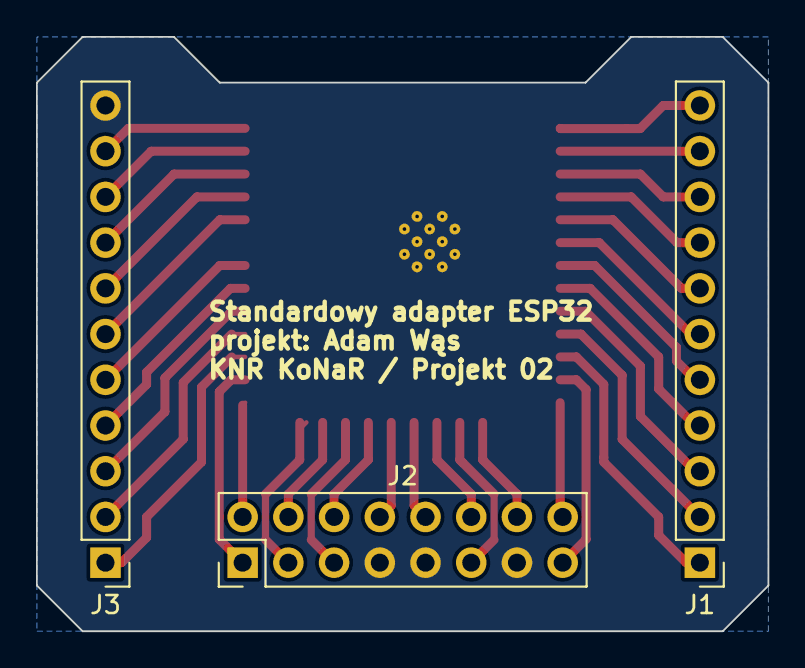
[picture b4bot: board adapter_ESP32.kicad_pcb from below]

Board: 2 copper layers, 40.6 x 33.0 mm, 5 parts (3 on the bottom side), 35 nets.

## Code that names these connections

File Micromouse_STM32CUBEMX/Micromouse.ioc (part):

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Mcu.Name=STM32F405RGTx
Mcu.Package=LQFP64
Mcu.UserName=STM32F405RGTx
PA0-WKUP.GPIOParameters=GPIO_Label
PA0-WKUP.GPIO_Label=PhotoT_6
PA0-WKUP.Signal=ADCx_IN0
PA1.GPIOParameters=GPIO_Label
PA1.GPIO_Label=PhotoT_5
PA1.Signal=ADCx_IN1
PA12.GPIOParameters=GPIO_Label
PA12.GPIO_Label=esp_spi_cs
PA12.Signal=GPIO_Output
PA13.Mode=Serial_Wire
PA13.Signal=SYS_JTMS-SWDIO
PA14.Mode=Serial_Wire
PA14.Signal=SYS_JTCK-SWCLK
PA2.GPIOParameters=GPIO_Label
PA2.GPIO_Label=PhotoT_4
PA2.Signal=ADCx_IN2
PA3.GPIOParameters=GPIO_Label
PA3.GPIO_Label=MotorR_PWM
PA3.Signal=S_TIM9_CH2
PA4.GPIOParameters=GPIO_Label
PA4.GPIO_Label=MotorR_AIN2
PA4.Signal=GPIO_Output
PA5.GPIOParameters=GPIO_Label
PA5.GPIO_Label=MotorR_AIN1
PA5.Signal=GPIO_Output
PA6.GPIOParameters=GPIO_Label
PA6.GPIO_Label=EMITTER_6
PA6.Signal=S_TIM3_CH1
PA7.GPIOParameters=GPIO_Label
PA7.GPIO_Label=EMITTER_5
PA7.Signal=S_TIM3_CH2
PA8.GPIOParameters=GPIO_Label
PA8.GPIO_Label=EMITTER_3
PA8.Signal=S_TIM1_CH1
PA9.GPIOParameters=GPIO_Label
PA9.GPIO_Label=EMITTER_4
PA9.Signal=S_TIM1_CH2
PB0.GPIOParameters=GPIO_Label
PB0.GPIO_Label=MotorL_PWM
PB0.Signal=S_TIM3_CH3
PB1.GPIOParameters=GPIO_Label
PB1.GPIO_Label=IMU_INT
PB1.Signal=GPXTI1
PB10.Mode=I2C
PB10.Signal=I2C2_SCL
PB11.Mode=I2C
PB11.Signal=I2C2_SDA
PB13.GPIOParameters=GPIO_Label
PB13.GPIO_Label=LD2
PB13.Signal=GPIO_Output
PB14.GPIOParameters=GPIO_Label
PB14.GPIO_Label=LD3
PB14.Signal=GPIO_Output
PB15.GPIOParameters=GPIO_PuPd,GPIO_Label
PB15.GPIO_Label=USER_BUTT1
PB15.GPIO_PuPd=GPIO_PULLUP
PB15.Signal=GPXTI15
PB2.GPIOParameters=GPIO_Label
PB2.GPIO_Label=DRDY
PB2.Signal=GPXTI2
PB3.Mode=Full_Duplex_Master
PB3.Signal=SPI1_SCK
PB4.Mode=Full_Duplex_Master
PB4.Signal=SPI1_MISO
PB5.Mode=Full_Duplex_Master
PB5.Signal=SPI1_MOSI
PB6.GPIOParameters=GPIO_Label
PB6.GPIO_Label=TIM_ENCODER_B1
PB6.Signal=S_TIM4_CH1
PB7.GPIOParameters=GPIO_Label
PB7.GPIO_Label=TIM_ENCODER_A1
PB7.Signal=S_TIM4_CH2
PB8.GPIOParameters=GPIO_Label
PB8.GPIO_Label=TIM_ENCODER_B2
PB8.Signal=S_TIM4_CH3
PB9.GPIOParameters=GPIO_Label
PB9.GPIO_Label=TIM_ENCODER_A2
PB9.Signal=S_TIM4_CH4
PC0.GPIOParameters=GPIO_Label
PC0.GPIO_Label=BATT_LVL
PC0.Signal=ADCx_IN10
PC1.GPIOParameters=GPIO_Label
PC1.GPIO_Label=PhotoT_1
PC1.Signal=ADCx_IN11
PC10.Mode=Asynchronous
PC10.Signal=UART4_TX
PC11.Mode=Asynchronous
PC11.Signal=UART4_RX
PC2.GPIOParameters=GPIO_Label
PC2.GPIO_Label=PhotoT_2
PC2.Signal=ADCx_IN12
PC3.GPIOParameters=GPIO_Label
PC3.GPIO_Label=PhotoT_3
PC3.Signal=ADCx_IN13
PC4.GPIOParameters=GPIO_Label
PC4.GPIO_Label=MotorL_BIN1
PC4.Signal=GPIO_Output
PC5.GPIOParameters=GPIO_Label
PC5.GPIO_Label=MotorL_BIN2
PC5.Signal=GPIO_Output
PC6.GPIOParameters=GPIO_PuPd,GPIO_Label
PC6.GPIO_Label=USER_BUTT2
PC6.GPIO_PuPd=GPIO_PULLUP
PC6.Signal=GPXTI6
PC8.GPIOParameters=GPIO_Label
PC8.GPIO_Label=EMITTER_1
PC8.Signal=S_TIM8_CH3
PC9.GPIOParameters=GPIO_Label
PC9.GPIO_Label=EMITTER_2
PC9.Signal=S_TIM3_CH4
PH0-OSC_IN.Mode=HSE-External-Oscillator
PH0-OSC_IN.Signal=RCC_OSC_IN
PH1-OSC_OUT.Mode=HSE-External-Oscillator
PH1-OSC_OUT.Signal=RCC_OSC_OUT
RCC.HSE_VALUE=16000000
RCC.SYSCLKFreq_VALUE=100000000
RCC.SYSCLKSource=RCC_SYSCLKSOURCE_PLLCLK
board=custom

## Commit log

2024-03-06 test
2024-03-07 cos tam cos tam
2024-03-07 working...
2024-03-07 DC driver
2024-03-07 trzeba dobrać bucka
2024-03-07 dodaję adaptery i ich footprinty
2024-03-07 Prawie skończone
2024-03-07 Pdf calej plytki
2024-03-08 druga wersja płytki stm32 do recenzji
2024-03-08 zapomniałem kilku ścieżek, teraz jest całość
2024-03-09 Dodaje wszystko nie chce mi sie z tym bawic
2024-03-09 Najnowzszy schemacik
2024-03-10 footprinty
2024-03-11 wstępnie zrobiony adapter ESP32-S3. oceń czy jest git to zrobię footprinta do niego
2024-03-11 drobne zmiany
2024-03-14 poprawione esp32s3
2024-03-14 folder footprintów
2024-03-28 Final version
2024-03-28 Removing some unnecessary files
2024-04-11 CubeMX project
2024-04-12 improving the hierarchical scheme
2024-04-12 changing engines
2024-04-15 CubeMX changes & raport
2024-04-16 Full schematics in pdf file
2024-05-04 DC motors driver
